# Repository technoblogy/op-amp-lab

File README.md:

# Pocket Op Amp Lab
A self-contained tool for experimenting with the configurable op amps in the AVR DB-series.

See http://www.technoblogy.com/show?3CHT.

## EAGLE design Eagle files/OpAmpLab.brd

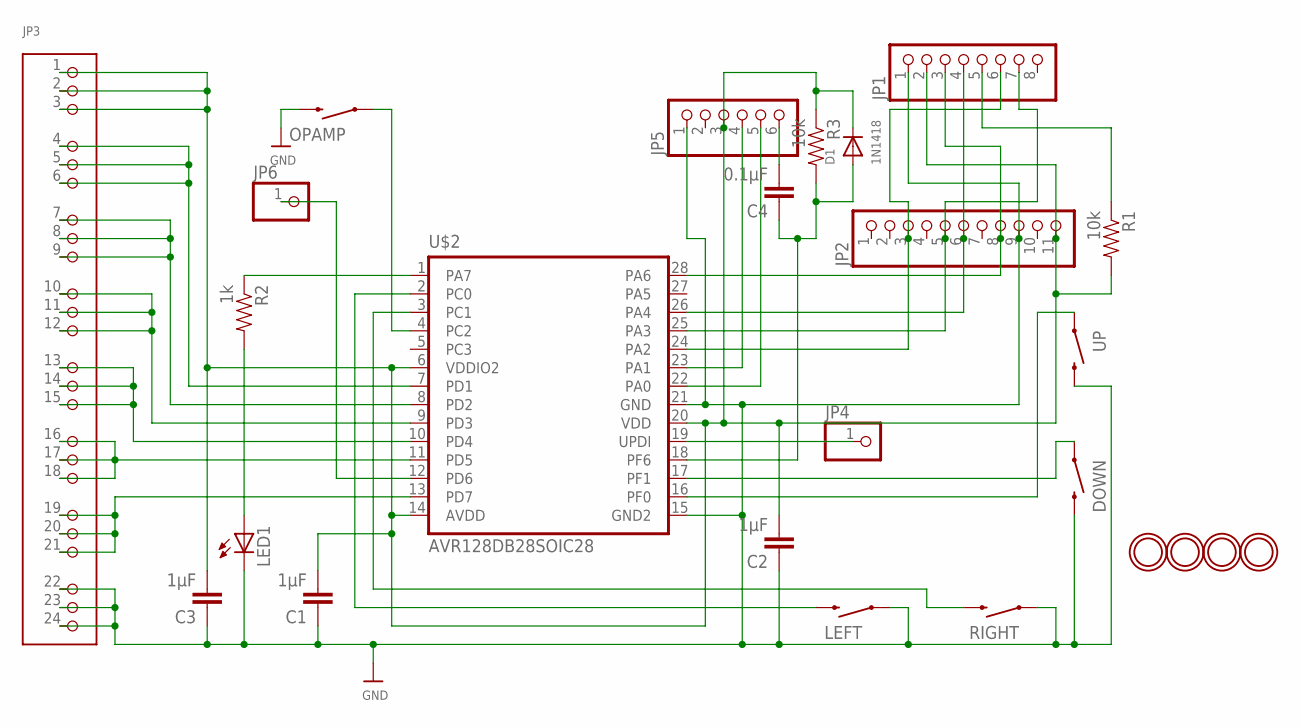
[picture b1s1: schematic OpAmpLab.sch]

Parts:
C1, C2, C3: 1µF; 0805
C4: 0.1µF; 0805
D1: 1N1418; SOD-323F
DOWN: SWITCH-MOMENTARY-2PTH; TACTILE-PTH
JP1: HEADER-1X8ROUND; 1X08_ROUND
JP2: HEADER-1X11; 1X11_ROUND
JP3: HEADER-3X08; 3X08
JP4, JP6: HEADER-1X1ROUND; 1X01_ROUND
JP5: HEADER-1X6ROUND; 1X06_ROUND
LED1: LEDCHIPLED_0805; CHIPLED_0805
LEFT: SWITCH-MOMENTARY-2PTH; TACTILE-PTH
OPAMP: SWITCH-MOMENTARY-2PTH; TACTILE-PTH
R1, R3: 10k; 0805
R2: 1k; 0805
RIGHT: SWITCH-MOMENTARY-2PTH; TACTILE-PTH
U$1, U$4, U$5, U$9: MOUNTINGHOLE2.5; MOUNTINGHOLE_2.5_PLATED
U$2: AVR128DB28SOIC28; SO-28W
UP: SWITCH-MOMENTARY-2PTH; TACTILE-PTH

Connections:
GND: C1.1, C2.1, C3.1, DOWN.3 (2), JP1.1, JP2.9, JP3.22, JP3.23, JP3.24, JP5.1, LED1.C, LEFT.1, OPAMP.3 (2), RIGHT.1, U$2.15 (GND2), U$2.21 (GND), UP.3 (2)
unnamed: JP4.1, U$2.19 (UPDI)
unnamed: JP1.7, JP2.5, U$2.25 (PA3)
unnamed: JP5.4, U$2.23 (PA1)
unnamed: JP1.5, R1.1
unnamed: JP1.3, JP2.8, U$2.28 (PA6)
unnamed: JP6.1, U$2.12 (PD6)
unnamed: OPAMP.1, U$2.4 (PC2)
unnamed: U$2.16 (PF0), UP.1
unnamed: R2.1, U$2.1 (PA7)
unnamed: DOWN.1, U$2.17 (PF1)
unnamed: JP3.4, JP3.5, JP3.6, U$2.7 (PD1)
unnamed: LEFT.3 (2), U$2.2 (PC0)
unnamed: RIGHT.3 (2), U$2.3 (PC1)
unnamed: JP3.7, JP3.8, JP3.9, U$2.8 (PD2)
unnamed: JP1.4, JP2.6, U$2.26 (PA4)
unnamed: JP1.6, JP2.3, U$2.24 (PA2)
unnamed: JP5.5, U$2.22 (PA0)
unnamed: JP3.10, JP3.11, JP3.12, U$2.9 (PD3)
unnamed: JP3.19, JP3.20, JP3.21, U$2.13 (PD7)
unnamed: JP3.13, JP3.14, JP3.15, U$2.10 (PD4)
unnamed: LED1.A, R2.2
unnamed: JP3.16, JP3.17, JP3.18, U$2.11 (PD5)
unnamed: C4.2, JP5.6
unnamed: C4.1, D1.A, R3.2, U$2.18 (PF6)
VDD: C1.2, C2.2, C3.2, D1.C, JP1.2, JP2.11, JP3.1, JP3.2, JP3.3, JP5.3, R1.2, R3.1, U$2.6 (VDDIO2), U$2.14 (AVDD), U$2.20 (VDD)

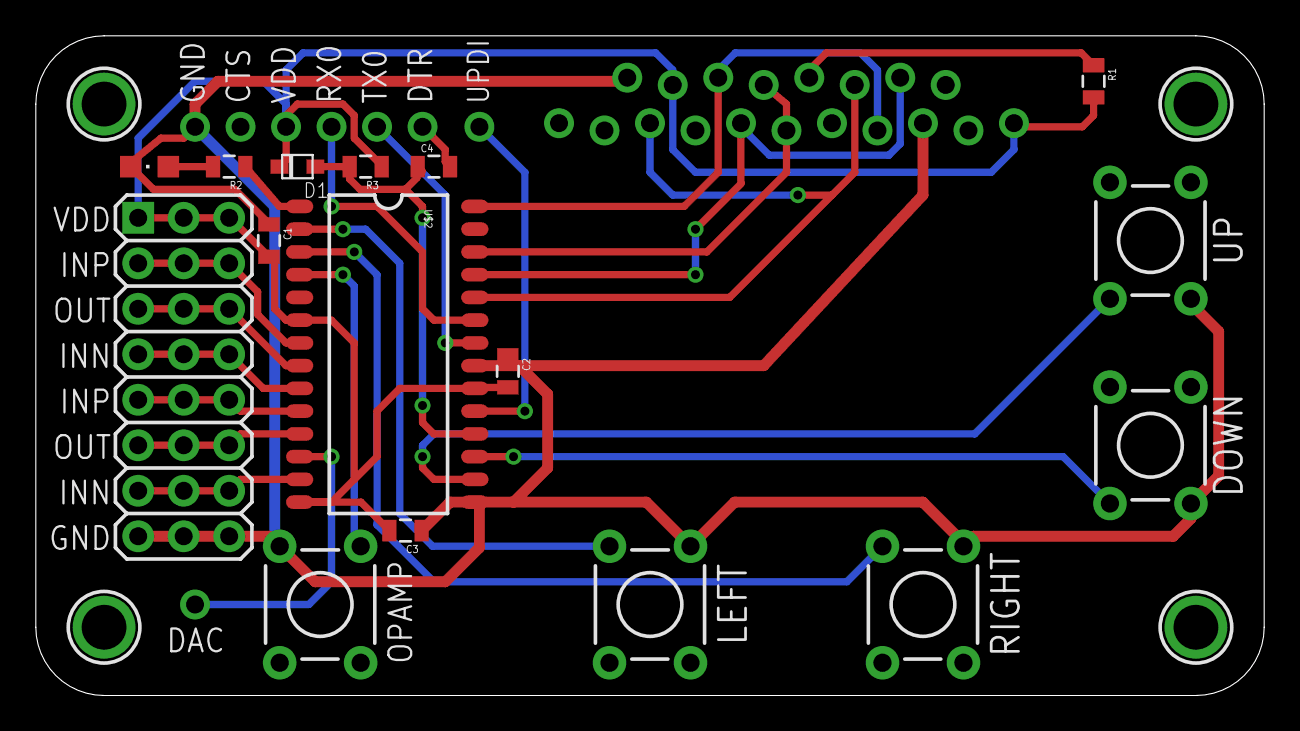
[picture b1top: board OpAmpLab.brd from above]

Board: 2 copper layers, 68.6 x 36.8 mm, 25 parts (0 on the bottom side), 26 nets.

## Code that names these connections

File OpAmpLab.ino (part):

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// Global UI settings
volatile int OpAmp = 0, Menu = 0;

const int LeftBtn = 8;   // PC0
const int RightBtn = 9;  // PC1
const int UpBtn = 20;    // PF0
const int DownBtn = 21;  // PF1

void InitButtons () {
  pinMode(LeftBtn, INPUT_PULLUP);
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
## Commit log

2021-01-13 Version 1 - 12th January 2021
2021-03-09 Added PCB files
2021-03-09 Added uLisp

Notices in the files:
OpAmpLab.ino:
CC BY 4.0
Licensed under a Creative Commons Attribution 4.0 International license:
http://creativecommons.org/licenses/by/4.0
parts and their libraries:
SparkFun-Electromechanical: Licensing: Creative Commons ShareAlike 4.0 International - https://creativecommons.org/licenses/by-sa/4.0
microbuilder: This work is placed in the public domain, and may be freely used for commercial and non-commercial work with the following conditions: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
